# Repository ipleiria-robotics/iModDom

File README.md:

# iModDom
*Inexpensive Modular Domotics*

O projeto iModDom consiste num ecossistema de *hardware* e *software* desenvolvido de forma a ser utilizado em conjunto para aplicações em domótica utilizando o [Home Assistant](https://www.home-assistant.io/ "Home Assistant") e o [ESPHome](https://esphome.io/ "ESPHome").
A parte de *hardware* do projeto consiste em três placas de circuito impresso desenvolvidas para albergar todos os componentes com o objetivo de obter uma solução compacta e de fácil utilização. Já a parte de *software* consiste numa página *web* desenvolvida para o projeto, onde contém ferramentas que possibilitam a programação, do respetivo *hardware*, através de blocos.
O projeto foi desenvolvido com o intuito e objetivo de ser uma solução económica e que permitisse a sua utilização aos utilizadores sem conhecimentos na área da programação.

## Passos a Seguir
- Recomenda-se que comece por consultar o manual técnico do projeto de modo a ficar a conhecer todos os componentes utilizados e o processo de montagem do *hardware*.
- Consulte os tutoriais disponíveis para poder usufruir do *software* desenvolvido.
- Faça as atividades propostas para ficar apto a criar as suas próprias aplicações para domótica.

## Ajuda
Se estiver com problemas, pode reportá-los [aqui](https://github.com/ipleiria-robotics/iModDom/issues "aqui").

## Contribuições 
Estamos abertos a sugestões com a finalidade de melhorar o projeto, pode colocá-las em forma de [pull request](https://github.com/ipleiria-robotics/iModDom/pulls "pull request") ou relatando os erros detetados.

# Autores
 - Marco Pereira - estudante do [Politécnico de Leiria](https://www.ipleiria.pt) do curso TeSP em Automação, Robótica e manutenção Industrial, GitHub: [MarcoPereira00](https://github.com/MarcoPereira00)

## Orientado por:
- Luís Conde - [Politécnico de Leiria](https://www.ipleiria.pt), GitHub:  [Luís Conde](https://github.com/conde-ISR-UC-PT)
- Carlos Neves - [Politécnico de Leiria](https://www.ipleiria.pt), [INESC-Coimbra](http://inescc.estg.ipleiria.pt/) GitHub:  [Carlos Neves](https://github.com/carlos-neves)

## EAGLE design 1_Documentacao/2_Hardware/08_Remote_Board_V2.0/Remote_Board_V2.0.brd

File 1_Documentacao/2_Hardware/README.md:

# iModDom
## *Hardware*
- Aqui estão disponíveis todos os ficheiros das placas de circuito impresso desenvolvidas através do *software Autodesk Eagle*. As placas contêm versões pelo que deverá sempre optar pela versão mais recente.
- Se desejar realizar alterações ao *hardware* desenvolvido tem todas as bibliotecas que foram utilizadas disponíveis na pasta [02_Eagle_Libraries](https://github.com/ipleiria-robotics/iModDom/tree/main/1_Documentacao/2_Hardware/02_Eagle_Libraries "02_Eagle_Libraries").
- Na pasta [01_Lista_de_Hardware](https://github.com/ipleiria-robotics/iModDom/blob/main/1_Documentacao/2_Hardware/01_Lista_de_Hardware "01_Lista_de_Hardware") pode verificar os custos do projeto de forma descriminada. Note que podem existir variações nos valores.
### Nota:
As versões V2.0 das placas, à presente data, não foram testadas nem fabricadas, pelo que a sua utilização e fabrico ficará à responsabilidade do utilizador. À exceção da versão V2.0 da *Shunt Board* que está totalmente funcional e testada.

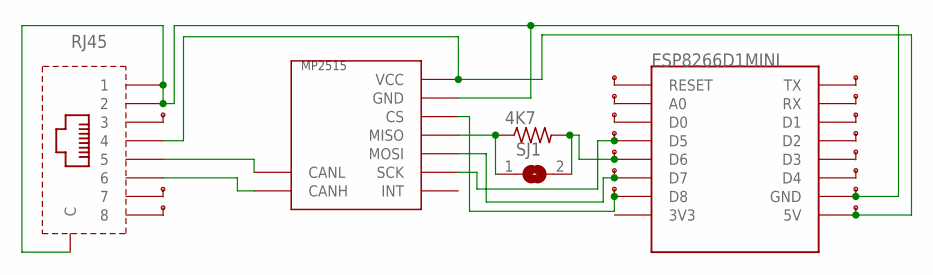
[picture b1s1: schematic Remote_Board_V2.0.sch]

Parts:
4K7: R-US_0207/10; 0207/10
ESP8266D1MINI: WEMOS-D1-MINI_SEM_LAYOUT
RJ45: ALI-RJ45_SEM_LAYOUT
SJ1: SJ
U$1, U$2, U$3, U$4, U$5, U$6, U$7, U$8, U$9, U$10, U$11, U$12, U$13, U$14, U$15, U$16, U$17, U$18: TP
U$31: MCP2515_MODULE_SEM_LAYOUT

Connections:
GND: ESP8266D1MINI.GND, RJ45.1, RJ45.2, RJ45.P$1 (C), RJ45.P$2 (C), U$15.P$1, U$31.GND
unnamed: RJ45.3, U$10.P$1
unnamed: RJ45.7, U$17.P$1
unnamed: RJ45.8, U$18.P$1
unnamed: ESP8266D1MINI.RESET, U$1.P$1
unnamed: ESP8266D1MINI.A0, U$2.P$1
unnamed: ESP8266D1MINI.D0, U$3.P$1
unnamed: ESP8266D1MINI.D5, U$4.P$1, U$31.SCK
unnamed: 4K7.2, ESP8266D1MINI.D6, SJ1.2, U$5.P$1
unnamed: ESP8266D1MINI.D7, U$8.P$1, U$31.MOSI
unnamed: ESP8266D1MINI.D8, U$9.P$1, U$31.CS
unnamed: RJ45.5, U$31.CL (CANL)
unnamed: RJ45.6, U$31.CH (CANH)
unnamed: ESP8266D1MINI.D4, U$14.P$1
unnamed: ESP8266D1MINI.D3, U$13.P$1
unnamed: ESP8266D1MINI.D2, U$12.P$1
unnamed: ESP8266D1MINI.D1, U$11.P$1
unnamed: ESP8266D1MINI.RX, U$7.P$1
unnamed: ESP8266D1MINI.TX, U$6.P$1
unnamed: 4K7.1, SJ1.1, U$31.MISO
unnamed: ESP8266D1MINI.5V, RJ45.4, U$16.P$1, U$31.VCC

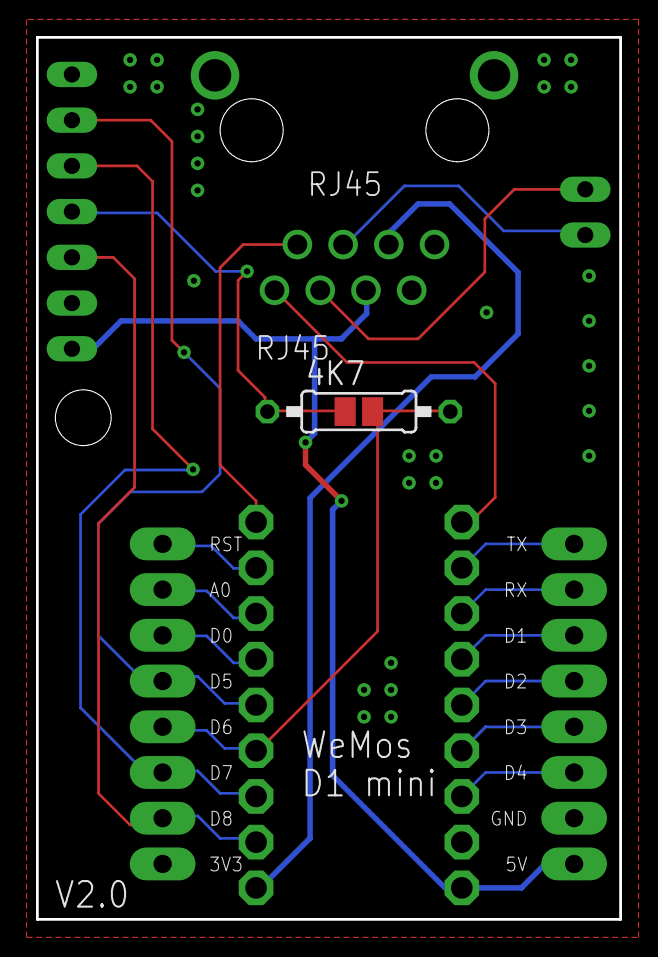
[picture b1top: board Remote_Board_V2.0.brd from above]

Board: 2 copper layers, 32.4 x 49.0 mm, 23 parts (0 on the bottom side), 21 nets.

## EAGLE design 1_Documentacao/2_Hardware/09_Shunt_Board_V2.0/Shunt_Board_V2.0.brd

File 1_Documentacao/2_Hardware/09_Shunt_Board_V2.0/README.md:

# iModDom
## *Shunt Board V2.0*
- Esta versão já foi fabricada e testada, pelo que se encontra totalmente funcional.

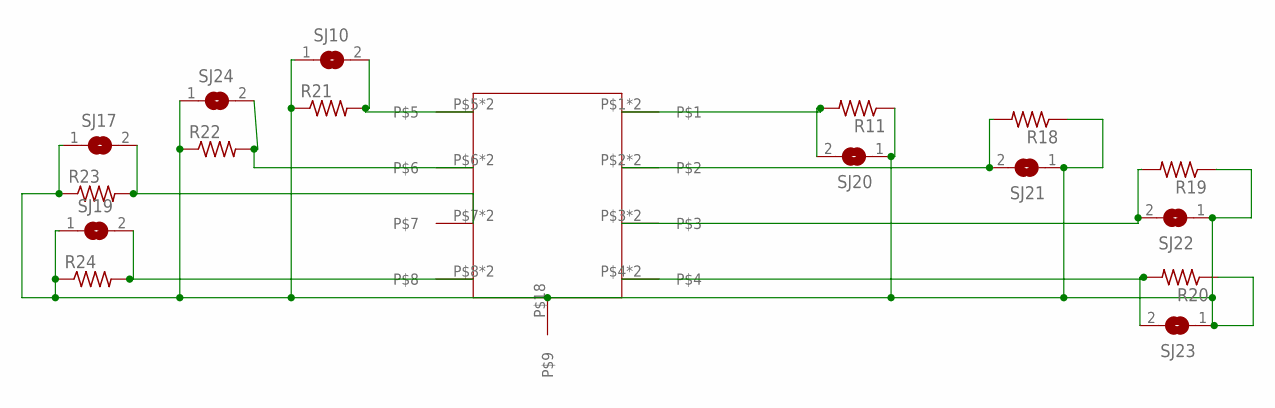
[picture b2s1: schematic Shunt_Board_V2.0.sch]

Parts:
R11, R18, R19, R20, R21, R22, R23, R24: R-US_0204/5; 0204/5
SJ10, SJ17, SJ19, SJ20, SJ21, SJ22, SJ23, SJ24: SJ
U$28: SHUNT2

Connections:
unnamed: R18.2, SJ21.2, U$28.P$2, U$28.P$11
unnamed: R19.2, SJ22.2, U$28.P$3, U$28.P$12
unnamed: R20.2, SJ23.2, U$28.P$4, U$28.P$13
unnamed: R21.2, SJ10.2, U$28.P$5, U$28.P$14
unnamed: R22.2, SJ24.2, U$28.P$6, U$28.P$15
unnamed: R23.2, SJ17.2, U$28.P$7, U$28.P$16
unnamed: R24.2, SJ19.2, U$28.P$8, U$28.P$17
unnamed: R11.1, R18.1, R19.1, R20.1, R21.1, R22.1, R23.1, R24.1, SJ10.1, SJ17.1, SJ19.1, SJ20.1, SJ21.1, SJ22.1, SJ23.1, SJ24.1, U$28.P$18
unnamed: R11.2, SJ20.2, U$28.P$1, U$28.P$10

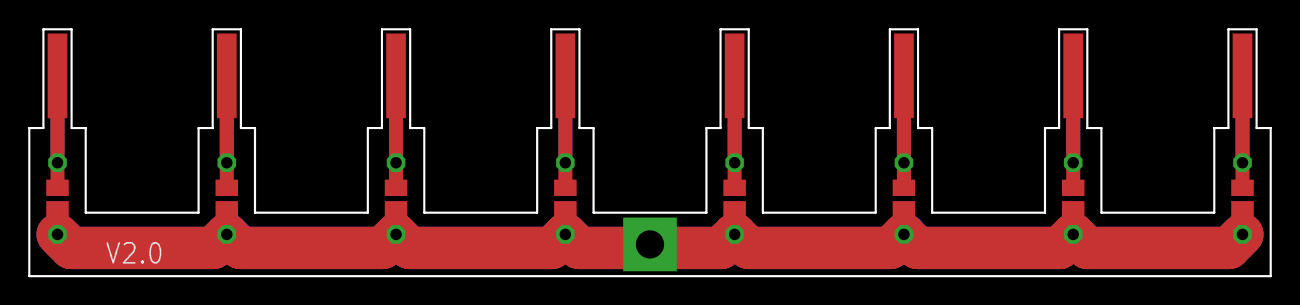
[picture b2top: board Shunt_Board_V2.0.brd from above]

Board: 2 copper layers, 88.0 x 17.5 mm, 17 parts (0 on the bottom side), 9 nets.

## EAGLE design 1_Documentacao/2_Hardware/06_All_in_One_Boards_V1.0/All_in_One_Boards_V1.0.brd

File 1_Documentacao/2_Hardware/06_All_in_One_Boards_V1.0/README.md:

# iModDom
## *All Boards V1.0*
- Nesta Pasta pode encontrar os ficheiros que permitem fabricar de forma facilitada todas as placas desenvolvidas relativas à versão V1.0.

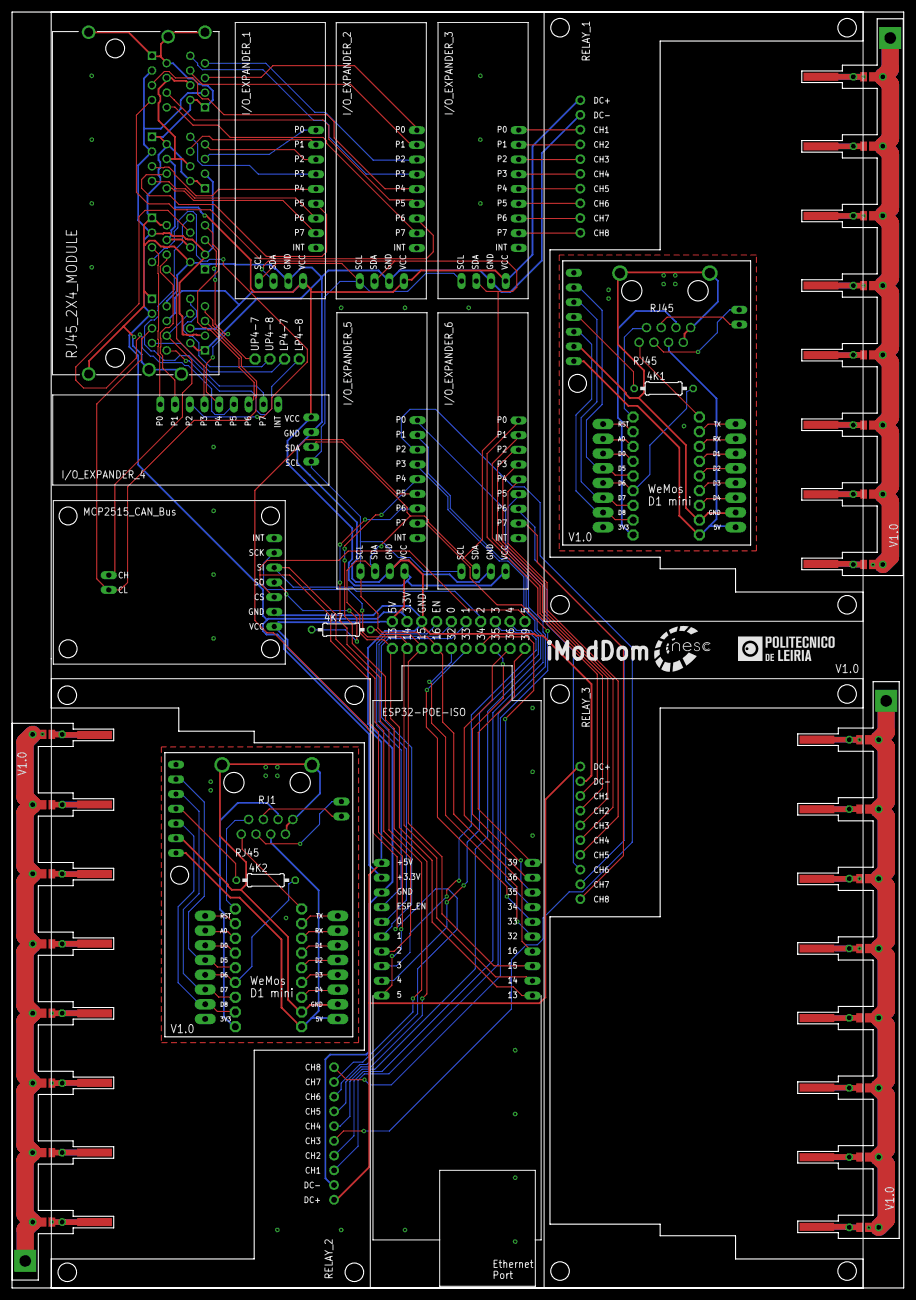
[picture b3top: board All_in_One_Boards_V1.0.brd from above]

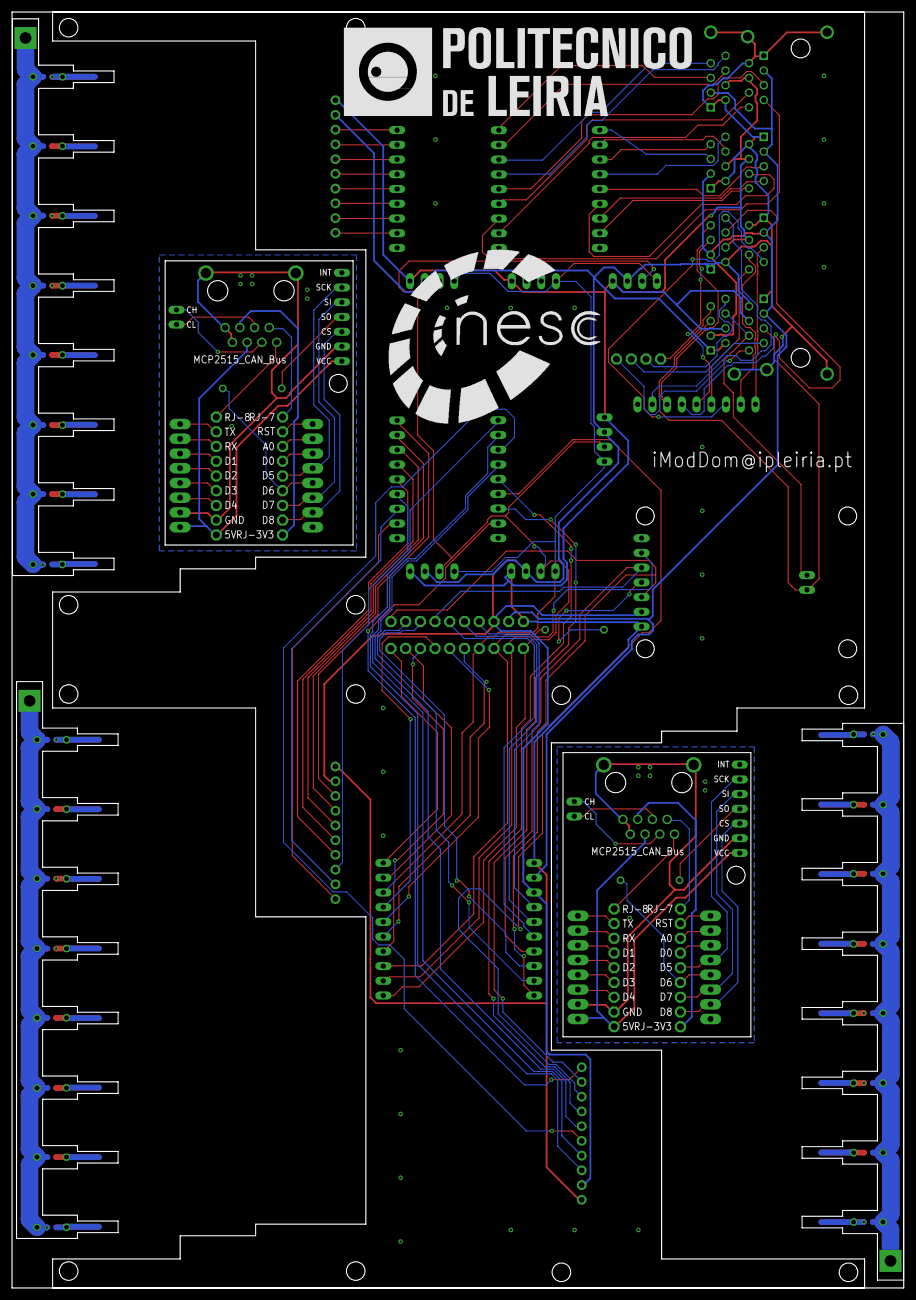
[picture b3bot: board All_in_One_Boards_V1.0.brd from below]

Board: 2 copper layers, 153.8 x 220.0 mm, 132 parts (8 on the bottom side), 144 nets.

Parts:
4K1, 4K2, 4K7: 0207/10
ESP32-POE-ISO: ESP-POE
ESP8266D1MINI, ESP8266D1MINI1: WEMOS-D1-MINI_SEM_LAYOUT
I/O_EXPANDER_1, I/O_EXPANDER_2, I/O_EXPANDER_3, I/O_EXPANDER_4, I/O_EXPANDER_5, I/O_EXPANDER_6: PCF8574-MODULE_ESPELHADO
R1, R2, R3, R4, R5, R6, R7, R8, R9, R10, R11, R12, R13, R14, R15, R16, R17, R18, R19, R20, R21, R22, R23, R24: 0204/5
RELAY_1, RELAY_2, RELAY_3: SSR_M_FULL_SEM_LIGACOES; SSR_M_SEM_LIGACOES
RJ1, RJ45: ALI-RJ45_SEM_LAYOUT
RJ45_2X4_MODULE: 5569262-1; TE_5569262-1
SJ1, SJ2, SJ3, SJ4, SJ5, SJ6, SJ7, SJ8, SJ9, SJ10, SJ11, SJ12, SJ13, SJ14, SJ15, SJ16, SJ17, SJ18, SJ19, SJ20, SJ21, SJ22, SJ23, SJ24: SJ
U$1, U$2, U$3, U$4, U$5, U$6, U$7, U$8, U$9, U$10, U$11, U$12, U$13, U$14, U$15, U$16, U$17, U$18, U$19, U$20, U$21, U$22, U$23, U$24, U$25, U$27, U$28, U$29, U$30, U$32, U$33, U$34, U$35, U$36, U$37, U$38, U$39, U$40, U$41, U$42, U$43, U$44, U$46, U$47, U$48, U$49, U$50, U$51, U$52, U$53, U$54, U$55, U$56, U$57, U$58, U$59, U$60, U$61, U$62, U$63: TP
U$26: MCP2515_MODULE_SEM_LIGACOES
U$31, U$45: MCP2515_MODULE_SEM_LAYOUT
U$64, U$65, U$66: SHUNT

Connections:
+3V3: ESP32-POE-ISO.3V3, RJ45_2X4_MODULE.LP1-3, RJ45_2X4_MODULE.LP2-3, RJ45_2X4_MODULE.LP3-3, RJ45_2X4_MODULE.LP4-3, RJ45_2X4_MODULE.UP1-3, RJ45_2X4_MODULE.UP2-3, RJ45_2X4_MODULE.UP3-3, RJ45_2X4_MODULE.UP4-3, U$6.P$1
+5V: ESP32-POE-ISO.5V, I/O_EXPANDER_1.VCC, I/O_EXPANDER_2.VCC, I/O_EXPANDER_3.VCC, I/O_EXPANDER_4.VCC, I/O_EXPANDER_5.VCC, I/O_EXPANDER_6.VCC, RELAY_1.DC+, RELAY_2.DC+, RELAY_3.DC+, RJ45_2X4_MODULE.LP1-4, RJ45_2X4_MODULE.LP2-4, RJ45_2X4_MODULE.LP3-4, RJ45_2X4_MODULE.LP4-4, RJ45_2X4_MODULE.UP1-4, RJ45_2X4_MODULE.UP2-4, RJ45_2X4_MODULE.UP3-4, RJ45_2X4_MODULE.UP4-4, U$2.P$1, U$26.VCC
GND: ESP32-POE-ISO.GND, I/O_EXPANDER_1.GND, I/O_EXPANDER_2.GND, I/O_EXPANDER_3.GND, I/O_EXPANDER_4.GND, I/O_EXPANDER_5.GND, I/O_EXPANDER_6.GND, RELAY_1.DC-, RELAY_2.DC-, RELAY_3.DC-, RJ45_2X4_MODULE.LP1-1, RJ45_2X4_MODULE.LP1-2, RJ45_2X4_MODULE.LP2-1, RJ45_2X4_MODULE.LP2-2, RJ45_2X4_MODULE.LP3-1, RJ45_2X4_MODULE.LP3-2, RJ45_2X4_MODULE.LP4-1, RJ45_2X4_MODULE.LP4-2, RJ45_2X4_MODULE.S1, RJ45_2X4_MODULE.S2, RJ45_2X4_MODULE.S3, RJ45_2X4_MODULE.S4, RJ45_2X4_MODULE.S5, RJ45_2X4_MODULE.S6, RJ45_2X4_MODULE.UP1-1, RJ45_2X4_MODULE.UP1-2, RJ45_2X4_MODULE.UP2-1, RJ45_2X4_MODULE.UP2-2, RJ45_2X4_MODULE.UP3-1, RJ45_2X4_MODULE.UP3-2, RJ45_2X4_MODULE.UP4-1, RJ45_2X4_MODULE.UP4-2, U$7.P$1, U$26.GND
GND1: ESP8266D1MINI.GND, RJ45.1, RJ45.2, RJ45.P$1, RJ45.P$2, U$31.GND, U$41.P$1
GND2: ESP8266D1MINI1.GND, RJ1.1, RJ1.2, RJ1.P$1, RJ1.P$2, U$45.GND, U$60.P$1
unnamed: I/O_EXPANDER_1.P7, RJ45_2X4_MODULE.LP2-8
unnamed: I/O_EXPANDER_1.P6, RJ45_2X4_MODULE.LP2-7
unnamed: I/O_EXPANDER_1.P5, RJ45_2X4_MODULE.LP2-6
unnamed: ESP32-POE-ISO.ESP_EN, U$8.P$1
unnamed: ESP32-POE-ISO.0, U$9.P$1
unnamed: ESP32-POE-ISO.1, U$10.P$1
unnamed: ESP32-POE-ISO.2, U$11.P$1, U$26.MOSI
unnamed: ESP32-POE-ISO.3, U$12.P$1
unnamed: ESP32-POE-ISO.4, U$13.P$1
unnamed: ESP32-POE-ISO.5, U$14.P$1, U$26.CS
unnamed: ESP32-POE-ISO.39, U$15.P$1
unnamed: ESP32-POE-ISO.36, U$16.P$1
unnamed: ESP32-POE-ISO.35, U$17.P$1
unnamed: ESP32-POE-ISO.34, U$18.P$1
unnamed: ESP32-POE-ISO.33, U$19.P$1
unnamed: ESP32-POE-ISO.32, U$20.P$1
unnamed: RJ45.3, U$34.P$1
unnamed: 4K7.2, ESP32-POE-ISO.15, U$22.P$1
unnamed: ESP32-POE-ISO.14, U$23.P$1, U$26.SCK
unnamed: RJ45.7, U$43.P$1
unnamed: I/O_EXPANDER_3.P0, RELAY_1.CH1
unnamed: I/O_EXPANDER_3.P1, RELAY_1.CH2
unnamed: I/O_EXPANDER_3.P2, RELAY_1.CH3
unnamed: I/O_EXPANDER_3.P3, RELAY_1.CH4
unnamed: I/O_EXPANDER_3.P4, RELAY_1.CH5
unnamed: I/O_EXPANDER_1.P4, RJ45_2X4_MODULE.LP2-5
unnamed: I/O_EXPANDER_3.P5, RELAY_1.CH6
unnamed: I/O_EXPANDER_3.P6, RELAY_1.CH7
unnamed: I/O_EXPANDER_3.P7, RELAY_1.CH8
unnamed: I/O_EXPANDER_6.P0, RELAY_3.CH1
unnamed: I/O_EXPANDER_6.P1, RELAY_3.CH2
unnamed: I/O_EXPANDER_6.P2, RELAY_3.CH3
unnamed: I/O_EXPANDER_6.P3, RELAY_3.CH4
unnamed: I/O_EXPANDER_6.P4, RELAY_3.CH5
unnamed: I/O_EXPANDER_6.P5, RELAY_3.CH6
unnamed: I/O_EXPANDER_6.P6, RELAY_3.CH7
unnamed: I/O_EXPANDER_6.P7, RELAY_3.CH8
unnamed: I/O_EXPANDER_5.P0, RELAY_2.CH1
unnamed: I/O_EXPANDER_5.P1, RELAY_2.CH2
unnamed: I/O_EXPANDER_5.P2, RELAY_2.CH3
unnamed: I/O_EXPANDER_5.P3, RELAY_2.CH4
unnamed: I/O_EXPANDER_5.P4, RELAY_2.CH5
unnamed: I/O_EXPANDER_5.P5, RELAY_2.CH6
unnamed: I/O_EXPANDER_5.P6, RELAY_2.CH7
unnamed: I/O_EXPANDER_5.P7, RELAY_2.CH8
unnamed: I/O_EXPANDER_1.P3, RJ45_2X4_MODULE.UP2-8
unnamed: I/O_EXPANDER_1.P2, RJ45_2X4_MODULE.UP2-7
unnamed: I/O_EXPANDER_1.P1, RJ45_2X4_MODULE.UP2-6
unnamed: I/O_EXPANDER_1.P0, RJ45_2X4_MODULE.UP2-5
unnamed: I/O_EXPANDER_2.P0, RJ45_2X4_MODULE.UP1-5
unnamed: I/O_EXPANDER_2.P1, RJ45_2X4_MODULE.UP1-6
unnamed: I/O_EXPANDER_2.P2, RJ45_2X4_MODULE.UP1-7
unnamed: I/O_EXPANDER_2.P3, RJ45_2X4_MODULE.UP1-8
unnamed: I/O_EXPANDER_2.P4, RJ45_2X4_MODULE.LP1-5
unnamed: I/O_EXPANDER_2.P5, RJ45_2X4_MODULE.LP1-6
unnamed: I/O_EXPANDER_2.P6, RJ45_2X4_MODULE.LP1-7
unnamed: I/O_EXPANDER_2.P7, RJ45_2X4_MODULE.LP1-8
unnamed: RJ45_2X4_MODULE.LP4-5, RJ45_2X4_MODULE.UP4-5, U$26.CL
unnamed: RJ45.8, U$44.P$1
unnamed: I/O_EXPANDER_4.P7, RJ45_2X4_MODULE.UP3-8
unnamed: I/O_EXPANDER_4.P6, RJ45_2X4_MODULE.UP3-7
unnamed: I/O_EXPANDER_4.P5, RJ45_2X4_MODULE.UP3-6
unnamed: I/O_EXPANDER_4.P4, RJ45_2X4_MODULE.UP3-5
unnamed: I/O_EXPANDER_4.P0, RJ45_2X4_MODULE.LP3-5
unnamed: I/O_EXPANDER_4.P1, RJ45_2X4_MODULE.LP3-6
unnamed: I/O_EXPANDER_4.P2, RJ45_2X4_MODULE.LP3-7
unnamed: I/O_EXPANDER_4.P3, RJ45_2X4_MODULE.LP3-8
unnamed: 4K7.1, U$26.MISO
unnamed: RJ45_2X4_MODULE.UP4-7, U$1.P$1
unnamed: RJ45_2X4_MODULE.UP4-8, U$4.P$1
unnamed: RJ45_2X4_MODULE.LP4-7, U$5.P$1
unnamed: RJ45_2X4_MODULE.LP4-8, U$25.P$1
unnamed: RJ45_2X4_MODULE.LP4-6, RJ45_2X4_MODULE.UP4-6, U$26.CH
unnamed: ESP8266D1MINI.RESET, U$3.P$1
unnamed: ESP8266D1MINI.A0, U$27.P$1
unnamed: ESP8266D1MINI.D0, U$28.P$1
unnamed: ESP8266D1MINI.D5, U$29.P$1, U$31.SCK
unnamed: 4K1.2, ESP8266D1MINI.D6, U$30.P$1
unnamed: ESP8266D1MINI.D7, U$31.MOSI, U$32.P$1
unnamed: ESP8266D1MINI.D8, U$31.CS, U$33.P$1
unnamed: ESP8266D1MINI.D4, U$40.P$1
unnamed: ESP8266D1MINI.D3, U$39.P$1
unnamed: ESP8266D1MINI.D2, U$38.P$1
unnamed: ESP8266D1MINI.D1, U$37.P$1
unnamed: ESP8266D1MINI.RX, U$36.P$1
unnamed: ESP8266D1MINI.TX, U$35.P$1
unnamed: ESP8266D1MINI.5V, RJ45.4, U$31.VCC, U$42.P$1
unnamed: RJ45.5, U$31.CL
unnamed: RJ45.6, U$31.CH
unnamed: 4K1.1, U$31.MISO
unnamed: RJ1.3, U$53.P$1
unnamed: RJ1.7, U$62.P$1
unnamed: RJ1.8, U$63.P$1
unnamed: ESP8266D1MINI1.RESET, U$46.P$1
unnamed: ESP8266D1MINI1.A0, U$47.P$1
unnamed: ESP8266D1MINI1.D0, U$48.P$1
unnamed: ESP8266D1MINI1.D5, U$45.SCK, U$49.P$1
unnamed: 4K2.2, ESP8266D1MINI1.D6, U$50.P$1
unnamed: ESP8266D1MINI1.D7, U$45.MOSI, U$51.P$1
unnamed: ESP8266D1MINI1.D8, U$45.CS, U$52.P$1
unnamed: ESP8266D1MINI1.D4, U$59.P$1
unnamed: ESP8266D1MINI1.D3, U$58.P$1
unnamed: ESP8266D1MINI1.D2, U$57.P$1
unnamed: ESP8266D1MINI1.D1, U$56.P$1
unnamed: ESP8266D1MINI1.RX, U$55.P$1
unnamed: ESP8266D1MINI1.TX, U$54.P$1
unnamed: ESP8266D1MINI1.5V, RJ1.4, U$45.VCC, U$61.P$1
unnamed: RJ1.5, U$45.CL
unnamed: RJ1.6, U$45.CH
unnamed: 4K2.1, U$45.MISO
unnamed: R18.2, SJ21.2, U$64.P$2
unnamed: R19.2, SJ22.2, U$64.P$3
unnamed: R20.2, SJ23.2, U$64.P$4
unnamed: R23.2, SJ17.2, U$64.P$7
unnamed: R24.2, SJ19.2, U$64.P$8
unnamed: R11.2, SJ20.2, U$64.P$1
unnamed: R21.2, SJ10.2, U$64.P$5
unnamed: R22.2, SJ24.2, U$64.P$6
unnamed: R11.1, R18.1, R19.1, R20.1, R21.1, R22.1, R23.1, R24.1, SJ10.1, SJ17.1, SJ19.1, SJ20.1, SJ21.1, SJ22.1, SJ23.1, SJ24.1, U$64.P$9
unnamed: R2.2, SJ5.2, U$65.P$2
unnamed: R3.2, SJ6.2, U$65.P$3
unnamed: R4.2, SJ7.2, U$65.P$4
unnamed: R7.2, SJ2.2, U$65.P$7
unnamed: R8.2, SJ3.2, U$65.P$8
unnamed: R1.2, SJ4.2, U$65.P$1
unnamed: R5.2, SJ1.2, U$65.P$5
unnamed: R6.2, SJ8.2, U$65.P$6
unnamed: R1.1, R2.1, R3.1, R4.1, R5.1, R6.1, R7.1, R8.1, SJ1.1, SJ2.1, SJ3.1, SJ4.1, SJ5.1, SJ6.1, SJ7.1, SJ8.1, U$65.P$9
unnamed: R10.2, SJ14.2, U$66.P$2
unnamed: R12.2, SJ15.2, U$66.P$3
unnamed: R13.2, SJ16.2, U$66.P$4
unnamed: R16.2, SJ11.2, U$66.P$7
unnamed: R17.2, SJ12.2, U$66.P$8
unnamed: R9.2, SJ13.2, U$66.P$1
unnamed: R14.2, SJ9.2, U$66.P$5
unnamed: R15.2, SJ18.2, U$66.P$6
unnamed: R9.1, R10.1, R12.1, R13.1, R14.1, R15.1, R16.1, R17.1, SJ9.1, SJ11.1, SJ12.1, SJ13.1, SJ14.1, SJ15.1, SJ16.1, SJ18.1, U$66.P$9
SCL: ESP32-POE-ISO.16, I/O_EXPANDER_1.SCL, I/O_EXPANDER_2.SCL, I/O_EXPANDER_3.SCL, I/O_EXPANDER_4.SCL, I/O_EXPANDER_5.SCL, I/O_EXPANDER_6.SCL, U$21.P$1
SDA: ESP32-POE-ISO.13, I/O_EXPANDER_1.SDA, I/O_EXPANDER_2.SDA, I/O_EXPANDER_3.SDA, I/O_EXPANDER_4.SDA, I/O_EXPANDER_5.SDA, I/O_EXPANDER_6.SDA, U$24.P$1

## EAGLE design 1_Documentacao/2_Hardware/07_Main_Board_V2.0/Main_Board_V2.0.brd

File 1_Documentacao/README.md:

# iModDom
## Documentação
- Nesta secção poderá encontrar toda a documentação do projeto, incluindo os ficheiros do *hardware* e *software* e ainda o manual técnico do projeto.

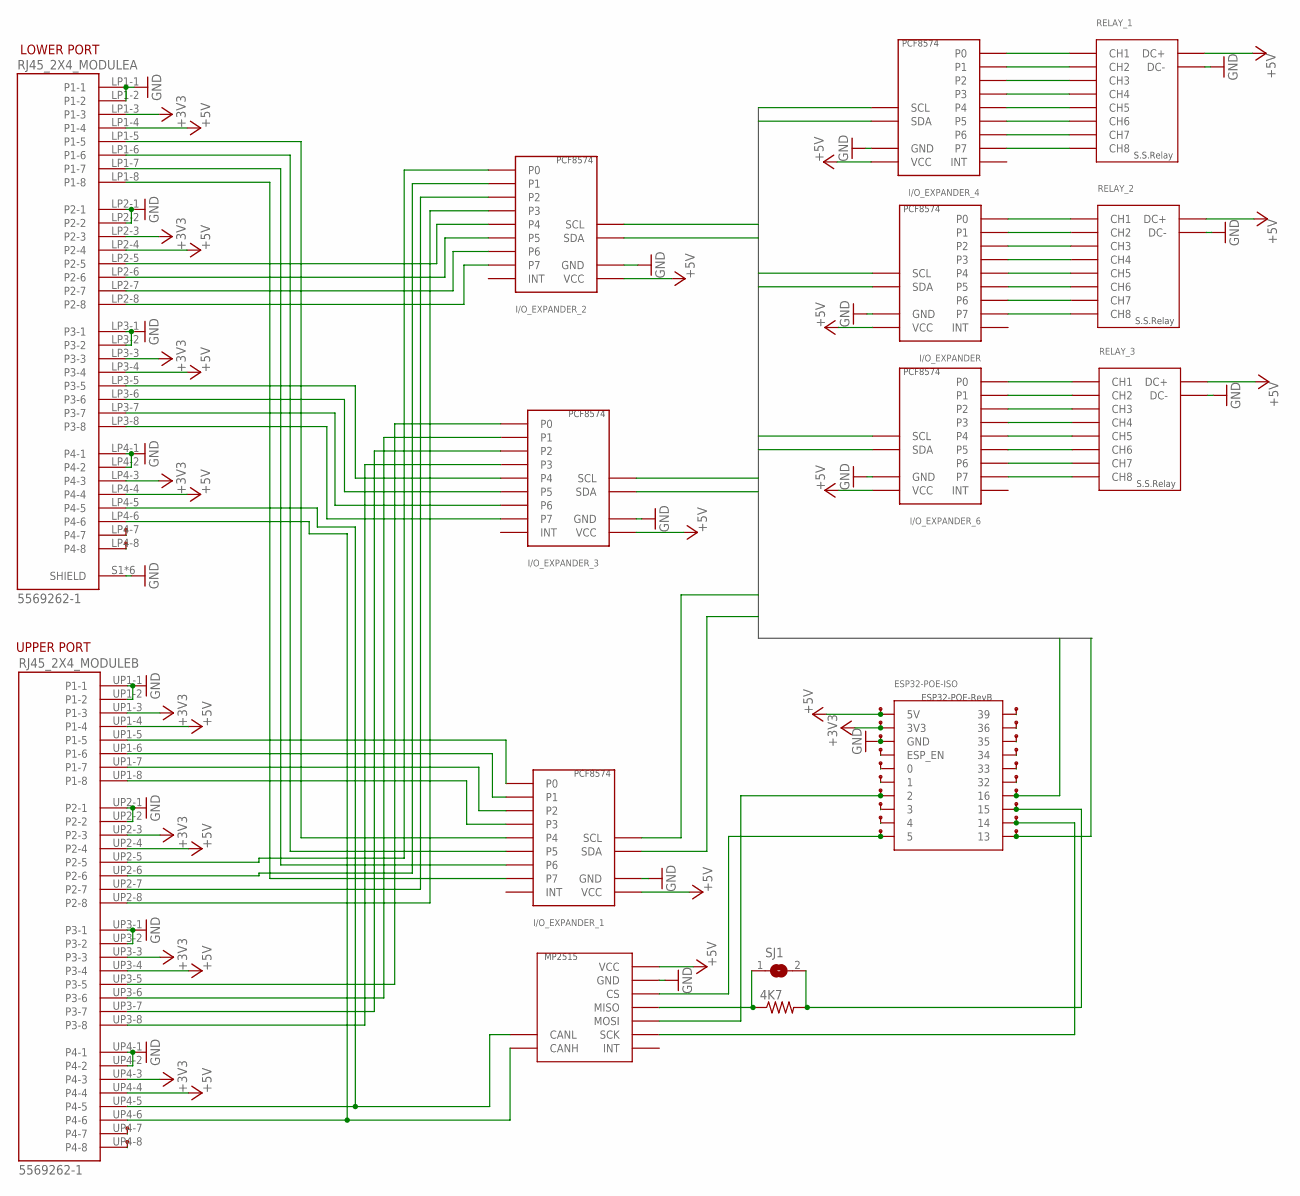
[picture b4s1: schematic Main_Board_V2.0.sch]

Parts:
4K7: R-US_0207/10; 0207/10
ESP32-POE-ISO: ESP-POE
I/O_EXPANDER: PCF8574-MODULE_ESPELHADO
I/O_EXPANDER_1, I/O_EXPANDER_2, I/O_EXPANDER_3, I/O_EXPANDER_4, I/O_EXPANDER_6: PCF8574-MODULE_ESPELHADO
RELAY_1, RELAY_2, RELAY_3: SSR_M_FULL_SEM_LIGACOES; SSR_M_SEM_LIGACOES
RJ45_2X4_MODULE: 5569262-1; TE_5569262-1
SJ1: SJ
U$1, U$2, U$4, U$5, U$6, U$7, U$8, U$9, U$10, U$11, U$12, U$13, U$14, U$15, U$16, U$17, U$18, U$19, U$20, U$21, U$22, U$23, U$24, U$25: TP
U$26: MCP2515_MODULE_SEM_LIGACOES

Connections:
+3V3: ESP32-POE-ISO.3V3, RJ45_2X4_MODULE.LP1-3 (P1-3), RJ45_2X4_MODULE.LP2-3 (P2-3), RJ45_2X4_MODULE.LP3-3 (P3-3), RJ45_2X4_MODULE.LP4-3 (P4-3), RJ45_2X4_MODULE.UP1-3 (P1-3), RJ45_2X4_MODULE.UP2-3 (P2-3), RJ45_2X4_MODULE.UP3-3 (P3-3), RJ45_2X4_MODULE.UP4-3 (P4-3), U$6.P$1
+5V: ESP32-POE-ISO.5V, I/O_EXPANDER.VCC, I/O_EXPANDER_1.VCC, I/O_EXPANDER_2.VCC, I/O_EXPANDER_3.VCC, I/O_EXPANDER_4.VCC, I/O_EXPANDER_6.VCC, RELAY_1.DC+, RELAY_2.DC+, RELAY_3.DC+, RJ45_2X4_MODULE.LP1-4 (P1-4), RJ45_2X4_MODULE.LP2-4 (P2-4), RJ45_2X4_MODULE.LP3-4 (P3-4), RJ45_2X4_MODULE.LP4-4 (P4-4), RJ45_2X4_MODULE.UP1-4 (P1-4), RJ45_2X4_MODULE.UP2-4 (P2-4), RJ45_2X4_MODULE.UP3-4 (P3-4), RJ45_2X4_MODULE.UP4-4 (P4-4), U$2.P$1, U$26.VCC
GND: ESP32-POE-ISO.GND, I/O_EXPANDER.GND, I/O_EXPANDER_1.GND, I/O_EXPANDER_2.GND, I/O_EXPANDER_3.GND, I/O_EXPANDER_4.GND, I/O_EXPANDER_6.GND, RELAY_1.DC-, RELAY_2.DC-, RELAY_3.DC-, RJ45_2X4_MODULE.LP1-1 (P1-1), RJ45_2X4_MODULE.LP1-2 (P1-2), RJ45_2X4_MODULE.LP2-1 (P2-1), RJ45_2X4_MODULE.LP2-2 (P2-2), RJ45_2X4_MODULE.LP3-1 (P3-1), RJ45_2X4_MODULE.LP3-2 (P3-2), RJ45_2X4_MODULE.LP4-1 (P4-1), RJ45_2X4_MODULE.LP4-2 (P4-2), RJ45_2X4_MODULE.S1 (SHIELD), RJ45_2X4_MODULE.S2 (SHIELD), RJ45_2X4_MODULE.S3 (SHIELD), RJ45_2X4_MODULE.S4 (SHIELD), RJ45_2X4_MODULE.S5 (SHIELD), RJ45_2X4_MODULE.S6 (SHIELD), RJ45_2X4_MODULE.UP1-1 (P1-1), RJ45_2X4_MODULE.UP1-2 (P1-2), RJ45_2X4_MODULE.UP2-1 (P2-1), RJ45_2X4_MODULE.UP2-2 (P2-2), RJ45_2X4_MODULE.UP3-1 (P3-1), RJ45_2X4_MODULE.UP3-2 (P3-2), RJ45_2X4_MODULE.UP4-1 (P4-1), RJ45_2X4_MODULE.UP4-2 (P4-2), U$7.P$1, U$26.GND
unnamed: I/O_EXPANDER_1.P0, RJ45_2X4_MODULE.UP1-5 (P1-5)
unnamed: I/O_EXPANDER_1.P1, RJ45_2X4_MODULE.UP1-6 (P1-6)
unnamed: I/O_EXPANDER_1.P2, RJ45_2X4_MODULE.UP1-7 (P1-7)
unnamed: ESP32-POE-ISO.ESP_EN, U$8.P$1
unnamed: ESP32-POE-ISO.0, U$9.P$1
unnamed: ESP32-POE-ISO.1, U$10.P$1
unnamed: ESP32-POE-ISO.2, U$11.P$1, U$26.MOSI
unnamed: ESP32-POE-ISO.3, U$12.P$1
unnamed: ESP32-POE-ISO.4, U$13.P$1
unnamed: ESP32-POE-ISO.5, U$14.P$1, U$26.CS
unnamed: ESP32-POE-ISO.39, U$15.P$1
unnamed: ESP32-POE-ISO.36, U$16.P$1
unnamed: ESP32-POE-ISO.35, U$17.P$1
unnamed: ESP32-POE-ISO.34, U$18.P$1
unnamed: ESP32-POE-ISO.33, U$19.P$1
unnamed: ESP32-POE-ISO.32, U$20.P$1
unnamed: I/O_EXPANDER_1.P3, RJ45_2X4_MODULE.UP1-8 (P1-8)
unnamed: 4K7.2, ESP32-POE-ISO.15, SJ1.2, U$22.P$1
unnamed: ESP32-POE-ISO.14, U$23.P$1, U$26.SCK
unnamed: I/O_EXPANDER_2.P0, RJ45_2X4_MODULE.UP2-5 (P2-5)
unnamed: I/O_EXPANDER_4.P0, RELAY_1.CH1
unnamed: I/O_EXPANDER_4.P1, RELAY_1.CH2
unnamed: I/O_EXPANDER_4.P2, RELAY_1.CH3
unnamed: I/O_EXPANDER_4.P3, RELAY_1.CH4
unnamed: I/O_EXPANDER_4.P4, RELAY_1.CH5
unnamed: I/O_EXPANDER_2.P1, RJ45_2X4_MODULE.UP2-6 (P2-6)
unnamed: I/O_EXPANDER_4.P5, RELAY_1.CH6
unnamed: I/O_EXPANDER_4.P6, RELAY_1.CH7
unnamed: I/O_EXPANDER_4.P7, RELAY_1.CH8
unnamed: I/O_EXPANDER_6.P0, RELAY_3.CH1
unnamed: I/O_EXPANDER_6.P1, RELAY_3.CH2
unnamed: I/O_EXPANDER_6.P2, RELAY_3.CH3
unnamed: I/O_EXPANDER_6.P3, RELAY_3.CH4
unnamed: I/O_EXPANDER_6.P4, RELAY_3.CH5
unnamed: I/O_EXPANDER_6.P5, RELAY_3.CH6
unnamed: I/O_EXPANDER_6.P6, RELAY_3.CH7
unnamed: I/O_EXPANDER_6.P7, RELAY_3.CH8
unnamed: I/O_EXPANDER.P0, RELAY_2.CH1
unnamed: I/O_EXPANDER.P1, RELAY_2.CH2
unnamed: I/O_EXPANDER.P2, RELAY_2.CH3
unnamed: I/O_EXPANDER.P3, RELAY_2.CH4
unnamed: I/O_EXPANDER.P4, RELAY_2.CH5
unnamed: I/O_EXPANDER.P5, RELAY_2.CH6
unnamed: I/O_EXPANDER.P6, RELAY_2.CH7
unnamed: I/O_EXPANDER.P7, RELAY_2.CH8
unnamed: I/O_EXPANDER_1.P4, RJ45_2X4_MODULE.LP1-5 (P1-5)
unnamed: I/O_EXPANDER_1.P5, RJ45_2X4_MODULE.LP1-6 (P1-6)
unnamed: I/O_EXPANDER_1.P6, RJ45_2X4_MODULE.LP1-7 (P1-7)
unnamed: I/O_EXPANDER_1.P7, RJ45_2X4_MODULE.LP1-8 (P1-8)
unnamed: I/O_EXPANDER_2.P2, RJ45_2X4_MODULE.UP2-7 (P2-7)
unnamed: I/O_EXPANDER_2.P3, RJ45_2X4_MODULE.UP2-8 (P2-8)
unnamed: I/O_EXPANDER_2.P4, RJ45_2X4_MODULE.LP2-5 (P2-5)
unnamed: I/O_EXPANDER_2.P5, RJ45_2X4_MODULE.LP2-6 (P2-6)
unnamed: I/O_EXPANDER_2.P6, RJ45_2X4_MODULE.LP2-7 (P2-7)
unnamed: I/O_EXPANDER_2.P7, RJ45_2X4_MODULE.LP2-8 (P2-8)
unnamed: 4K7.1, SJ1.1, U$26.MISO
unnamed: I/O_EXPANDER_3.P0, RJ45_2X4_MODULE.UP3-5 (P3-5)
unnamed: RJ45_2X4_MODULE.LP4-5 (P4-5), RJ45_2X4_MODULE.UP4-5 (P4-5), U$26.CL (CANL)
unnamed: I/O_EXPANDER_3.P1, RJ45_2X4_MODULE.UP3-6 (P3-6)
unnamed: I/O_EXPANDER_3.P2, RJ45_2X4_MODULE.UP3-7 (P3-7)
unnamed: I/O_EXPANDER_3.P3, RJ45_2X4_MODULE.UP3-8 (P3-8)
unnamed: I/O_EXPANDER_3.P4, RJ45_2X4_MODULE.LP3-5 (P3-5)
unnamed: I/O_EXPANDER_3.P5, RJ45_2X4_MODULE.LP3-6 (P3-6)
unnamed: I/O_EXPANDER_3.P6, RJ45_2X4_MODULE.LP3-7 (P3-7)
unnamed: I/O_EXPANDER_3.P7, RJ45_2X4_MODULE.LP3-8 (P3-8)
unnamed: RJ45_2X4_MODULE.UP4-7 (P4-7), U$1.P$1
unnamed: RJ45_2X4_MODULE.UP4-8 (P4-8), U$4.P$1
unnamed: RJ45_2X4_MODULE.LP4-7 (P4-7), U$5.P$1
unnamed: RJ45_2X4_MODULE.LP4-8 (P4-8), U$25.P$1
unnamed: RJ45_2X4_MODULE.LP4-6 (P4-6), RJ45_2X4_MODULE.UP4-6 (P4-6), U$26.CH (CANH)
SCL: ESP32-POE-ISO.16, I/O_EXPANDER.SCL, I/O_EXPANDER_1.SCL, I/O_EXPANDER_2.SCL, I/O_EXPANDER_3.SCL, I/O_EXPANDER_4.SCL, I/O_EXPANDER_6.SCL, U$21.P$1
SDA: ESP32-POE-ISO.13, I/O_EXPANDER.SDA, I/O_EXPANDER_1.SDA, I/O_EXPANDER_2.SDA, I/O_EXPANDER_3.SDA, I/O_EXPANDER_4.SDA, I/O_EXPANDER_6.SDA, U$24.P$1

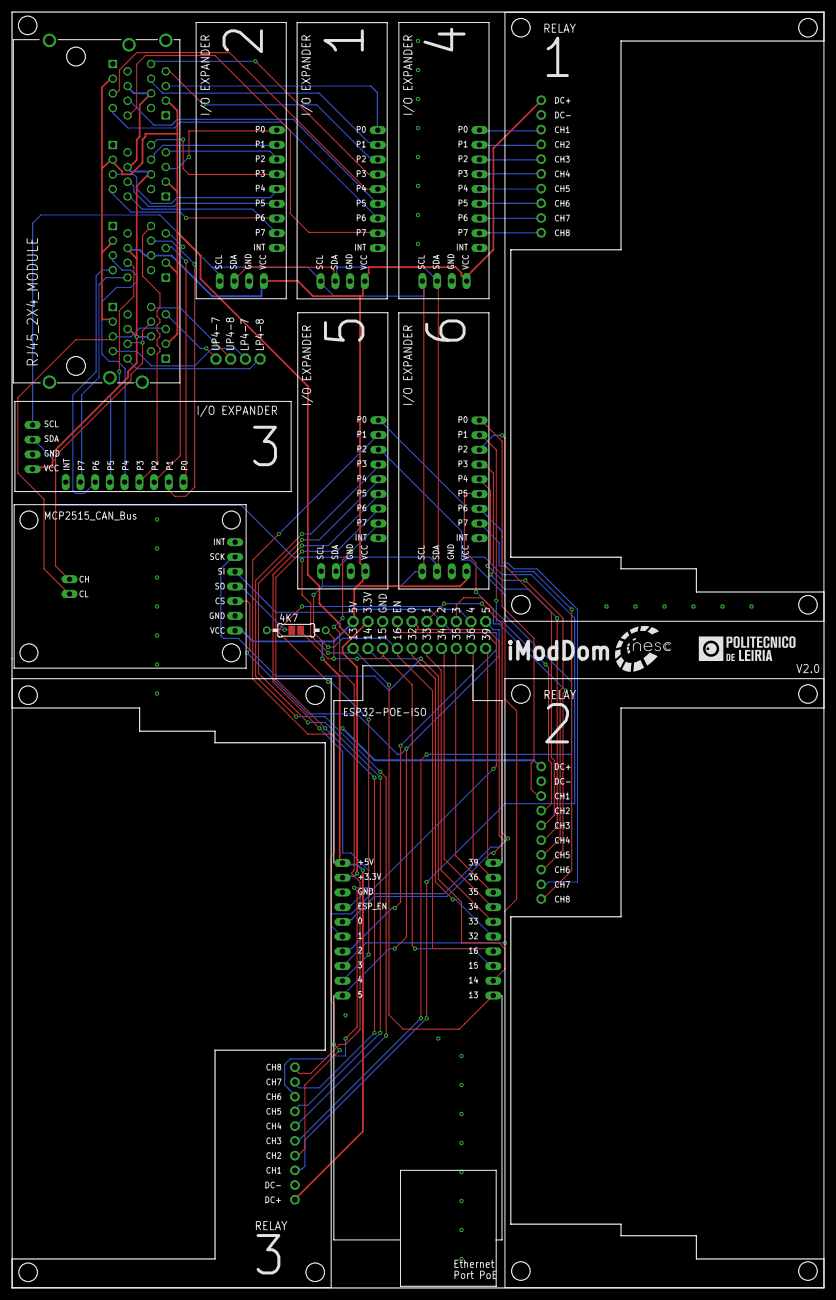
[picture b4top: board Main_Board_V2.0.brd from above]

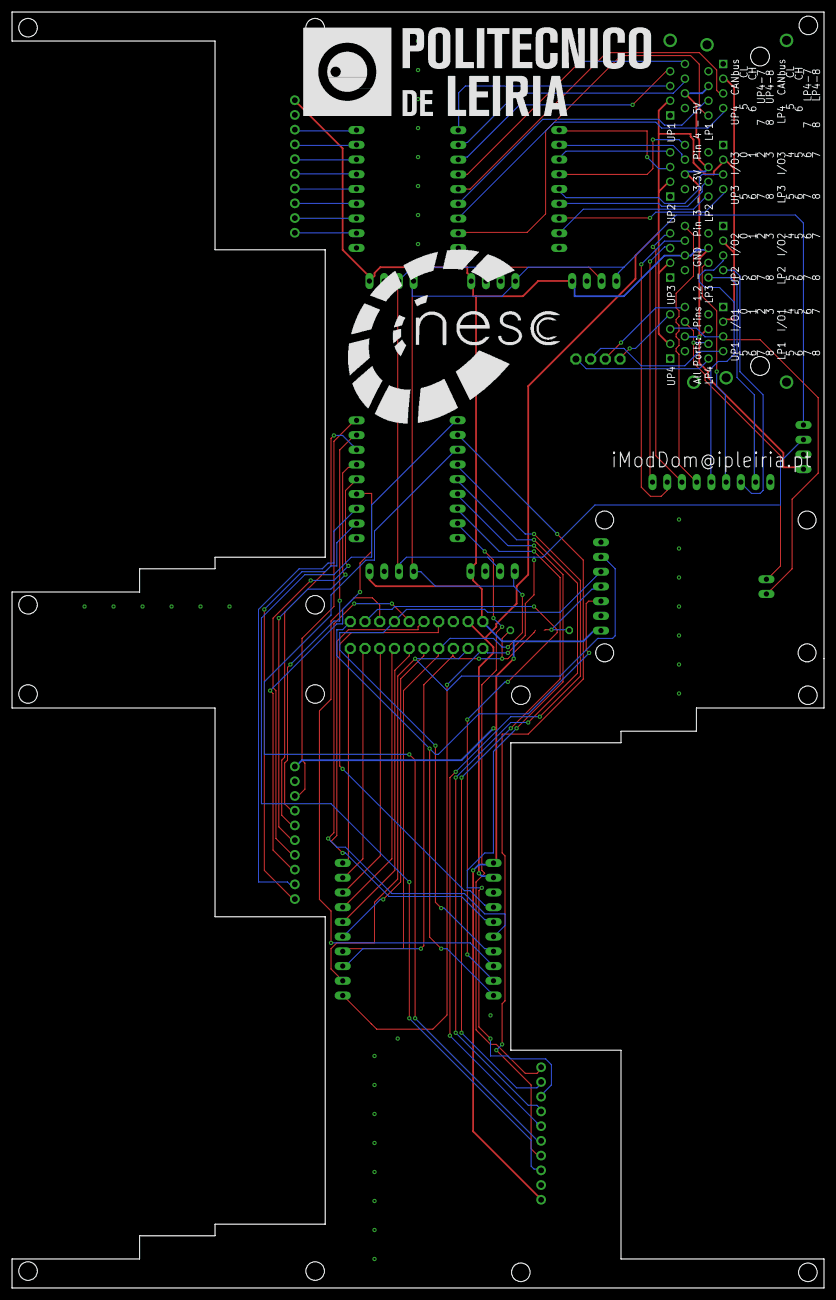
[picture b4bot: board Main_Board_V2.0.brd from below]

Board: 2 copper layers, 140.0 x 220.0 mm, 38 parts (5 on the bottom side), 75 nets.

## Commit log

2021-07-03 First Upload
2021-11-02 Update Hardware Files
2021-11-02 Update Eagle Libraries
2021-11-04 Update All in One Boards
